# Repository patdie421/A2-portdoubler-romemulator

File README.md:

This card provide 2 functionalities :  
- duplicates the slot it uses into two horizontal slots (usefull in slot 7). I designed it to be able to use an A2DVI interface on Apple II computers where all the slots are occupied.  
- ROM emulation card (https://mirrors.apple2.org.za/ftp.apple.asimov.net/documentation/hardware/schematics/rom_emulator_card_050-0009-01_schematic.pdf). A friend ask me for a card capable of running Adrian Black's Deadtest ROM (https://github.com/misterblack1/appleII_deadtest). Since I had space on my slot splitter, I simply added three chips, and that was it. This first version is designed to use only the Deadtest ROM. Current restriction :
  - it did'nt allow to be controled by softwitch  
  - DMA IN/OUT are not supported (not needed when used in slot 7)  

  A version of the card currently under development will provide all the functionalities of a ROM card  
# Slot doubler  
This card is designed to allow the installation of two cards in a single slot. Although it can be installed in any slot, it is most effectively used as a splitter in slot 7. Since the two connectors are wired in parallel, not all card combinations are possible.
## kinds of Apple II cards
We can identify 3 kinds of cards :
- basic card : use soft switches, 16 addresses 0xC080+n\*0x10 to 0xC08F+n\*0x10, n=1 to 7, to interact whith the system. The card is activated by "Device Select" line.
- card with firmware locate at Cn00-CnFF (n=1 to 7), the "I/O Select" activated this kind of card when the firmware page is read or write. Most of this cards (if not all) use also soft switches at addresses C0N0x.  
- card "monitoring" the address bus (does not use device selection or I/O selection).  

## possible combinaisons

Different factors limit possible combinations :
- kind of card
- DMA or Interrupts
Other factors limit this combination, including the use of DMA and interrupt lines (/NMI and /INT).  
Before trying to install 2 cards in the doubled slots you have to know witch kind of cards you have.  

## working (tested) combinaisons
(to be done)

(usefull information can be fund here : https://grokipedia.com/page/apple_ii_peripheral_cards)

# Rom emulation card
The rom is activated when a jumper is set on JP4. Current version can only be used for Apple II deadtest ROM.  
Work is in progress to emulate all functionalities of Apple Rom Emulator Card (050-0009-01)  (https://mirrors.apple2.org.za/Apple%20II%20Documentation%20Project/Interface%20Cards/ROM%20Cards/Apple%20ROM%20Emulator%20Card/Photos/Apple%20ROM%20Card%20with%20ROM%20-%20Front.jpg))

2764 or 27128 Eprom (or pinout equivalent) can be used. Check Adrian's documentation for burning the ROM. Not that for 8K ROM (2764) you have to load into address $1800 or for 16K ROM (27128) to $3800.

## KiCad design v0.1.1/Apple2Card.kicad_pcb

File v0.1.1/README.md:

Update connector positions  
  
 Not tested now

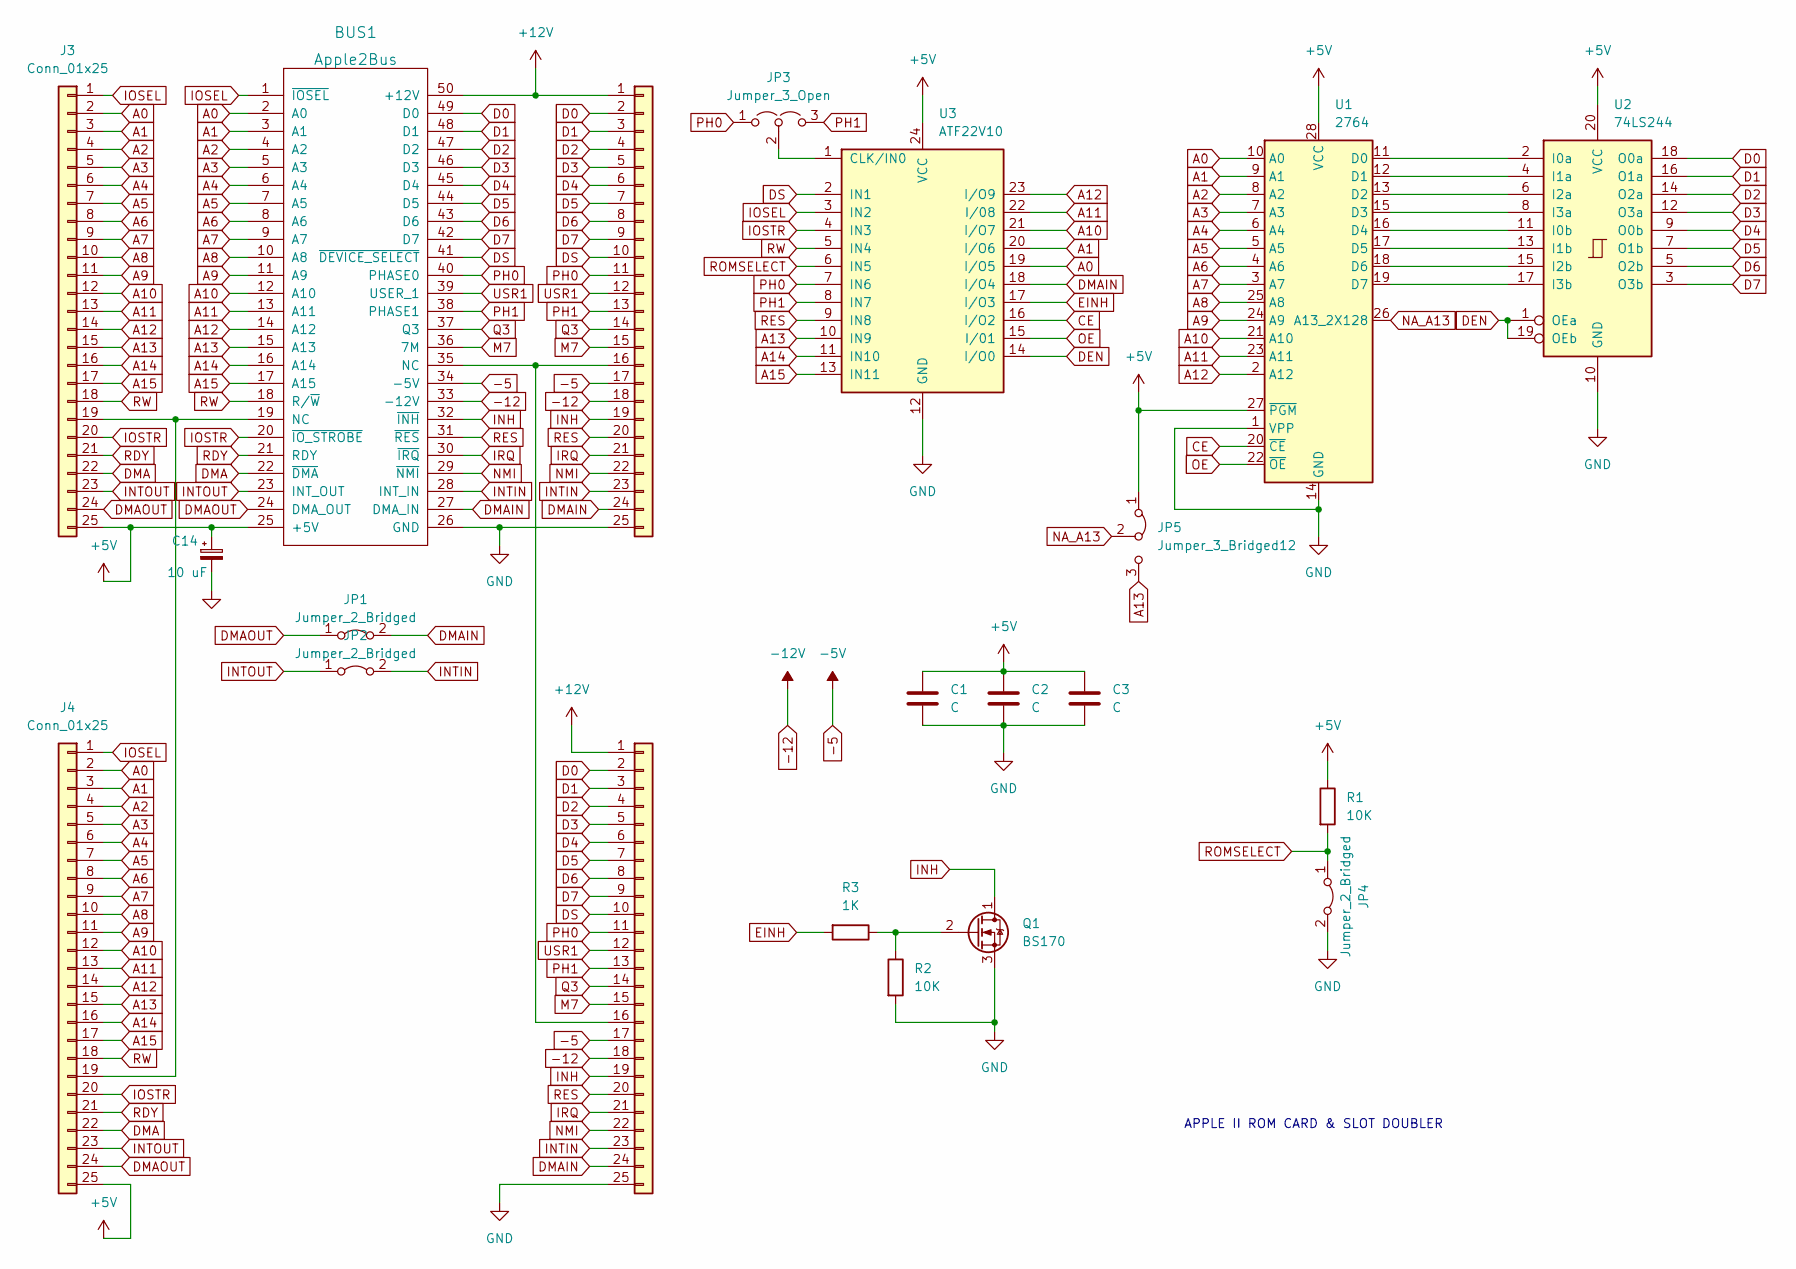
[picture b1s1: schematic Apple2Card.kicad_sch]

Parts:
BUS1: Apple2Bus; Apple2Slot
C1, C2, C3: C; C_Disc_D4.7mm_W2.5mm_P5.00mm
C14: 10 uF; CP_Radial_D5.0mm_P2.50mm
J1, J2, J3, J4: Conn_01x25; PinHeader_1x25_P2.54mm_Vertical
JP1, JP2, JP4: Jumper_2_Bridged; PinHeader_1x02_P2.54mm_Vertical
JP3: Jumper_3_Open; PinHeader_1x03_P2.54mm_Vertical
JP5: Jumper_3_Bridged12; SolderJumper-3_P1.3mm_Bridged12_RoundedPad1.0x1.5mm
Q1: BS170; TO-92_Inline
R1, R2: 10K; R_Axial_DIN0204_L3.6mm_D1.6mm_P7.62mm_Horizontal
R3: 1K; R_Axial_DIN0204_L3.6mm_D1.6mm_P7.62mm_Horizontal
U1: 2764; DIP-28_W15.24mm
U2: 74LS244; DIP-20_W7.62mm_Socket
U3: ATF22V10; DIP-24_W7.62mm_Socket

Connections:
+5V: BUS1.25 (+5V), C1.1, C2.1, C3.1, C14.1, J3.25, J4.25, JP5.1 (A), R1.1, U1.27 (~PGM), U1.28 (VCC), U2.20 (VCC), U3.24 (VCC)
+12V: BUS1.50 (+12V), J1.1, J2.1
-5: BUS1.34 (-5V), J1.17, J2.17
-12: BUS1.33 (-12V), J1.18, J2.18
A0: BUS1.2 (A0), J3.2, J4.2, U1.10 (A0), U3.19 (I/O5)
A1: BUS1.3 (A1), J3.3, J4.3, U1.9 (A1), U3.20 (I/O6)
A2: BUS1.4 (A2), J3.4, J4.4, U1.8 (A2)
A3: BUS1.5 (A3), J3.5, J4.5, U1.7 (A3)
A4: BUS1.6 (A4), J3.6, J4.6, U1.6 (A4)
A5: BUS1.7 (A5), J3.7, J4.7, U1.5 (A5)
A6: BUS1.8 (A6), J3.8, J4.8, U1.4 (A6)
A7: BUS1.9 (A7), J3.9, J4.9, U1.3 (A7)
A8: BUS1.10 (A8), J3.10, J4.10, U1.25 (A8)
A9: BUS1.11 (A9), J3.11, J4.11, U1.24 (A9)
A10: BUS1.12 (A10), J3.12, J4.12, U1.21 (A10), U3.21 (I/O7)
A11: BUS1.13 (A11), J3.13, J4.13, U1.23 (A11), U3.22 (I/08)
A12: BUS1.14 (A12), J3.14, J4.14, U1.2 (A12), U3.23 (I/O9)
A13: BUS1.15 (A13), J3.15, J4.15, JP5.3 (B), U3.10 (IN9)
A14: BUS1.16 (A14), J3.16, J4.16, U3.11 (IN10)
A15: BUS1.17 (A15), J3.17, J4.17, U3.13 (IN11)
CE: U1.20 (~CE), U3.16 (I/O2)
D0: BUS1.49 (D0), J1.2, J2.2, U2.18 (O0a)
D1: BUS1.48 (D1), J1.3, J2.3, U2.16 (O1a)
D2: BUS1.47 (D2), J1.4, J2.4, U2.14 (O2a)
D3: BUS1.46 (D3), J1.5, J2.5, U2.12 (O3a)
D4: BUS1.45 (D4), J1.6, J2.6, U2.9 (O0b)
D5: BUS1.44 (D5), J1.7, J2.7, U2.7 (O1b)
D6: BUS1.43 (D6), J1.8, J2.8, U2.5 (O2b)
D7: BUS1.42 (D7), J1.9, J2.9, U2.3 (O3b)
DEN: U2.1 (OEa), U2.19 (OEb), U3.14 (I/O0)
DMA: BUS1.22 (~DMA), J3.22, J4.22
DMAIN: BUS1.27 (DMA_IN), J1.24, J2.24, JP1.2 (B), U3.18 (I/O4)
DMAOUT: BUS1.24 (DMA_OUT), J3.24, J4.24, JP1.1 (A)
DS: BUS1.41 (~DEVICE_SELECT), J1.10, J2.10, U3.2 (IN1)
EINH: R3.2, U3.17 (I/O3)
GND: BUS1.26 (GND), C1.2, C2.2, C3.2, C14.2, J1.25, J2.25, JP4.2 (B), Q1.3 (S), R2.2, U1.1 (VPP), U1.14 (GND), U2.10 (GND), U3.12 (GND)
INH: BUS1.32 (~INH), J1.19, J2.19, Q1.1 (D)
INTIN: BUS1.28 (INT_IN), J1.23, J2.23, JP2.2 (B)
INTOUT: BUS1.23 (INT_OUT), J3.23, J4.23, JP2.1 (A)
IOSEL: BUS1.1 (~IOSEL), J3.1, J4.1, U3.3 (IN2)
IOSTR: BUS1.20 (~IO_STROBE), J3.20, J4.20, U3.4 (IN3)
IRQ: BUS1.30 (~IRQ), J1.21, J2.21
M7: BUS1.36 (7M), J1.15, J2.15
NA_A13: JP5.2 (C), U1.26 (A13_2X128)
NMI: BUS1.29 (~NMI), J1.22, J2.22
unnamed: BUS1.35 (NC), J1.16, J2.16
unnamed: BUS1.19 (NC), J3.19, J4.19
unnamed: JP3.2 (C), U3.1 (CLK/IN0)
unnamed: Q1.2 (G), R2.1, R3.1
unnamed: U1.11 (D0), U2.2 (I0a)
unnamed: U1.12 (D1), U2.4 (I1a)
unnamed: U1.13 (D2), U2.6 (I2a)
unnamed: U1.15 (D3), U2.8 (I3a)
unnamed: U1.16 (D4), U2.11 (I0b)
unnamed: U1.17 (D5), U2.13 (I1b)
unnamed: U1.18 (D6), U2.15 (I2b)
unnamed: U1.19 (D7), U2.17 (I3b)
OE: U1.22 (~OE), U3.15 (I/01)
PH0: BUS1.40 (PHASE0), J1.11, J2.11, JP3.1 (A), U3.7 (IN6)
PH1: BUS1.38 (PHASE1), J1.13, J2.13, JP3.3 (B), U3.8 (IN7)
Q3: BUS1.37 (Q3), J1.14, J2.14
RDY: BUS1.21 (RDY), J3.21, J4.21
RES: BUS1.31 (~RES), J1.20, J2.20, U3.9 (IN8)
RW: BUS1.18 (R/~W), J3.18, J4.18, U3.5 (IN4)
USR1: BUS1.39 (USER_1), J1.12, J2.12
/ROMSELECT: JP4.1 (A), R1.2, U3.6 (IN5)

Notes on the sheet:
APPLE II ROM CARD & SLOT DOUBLER

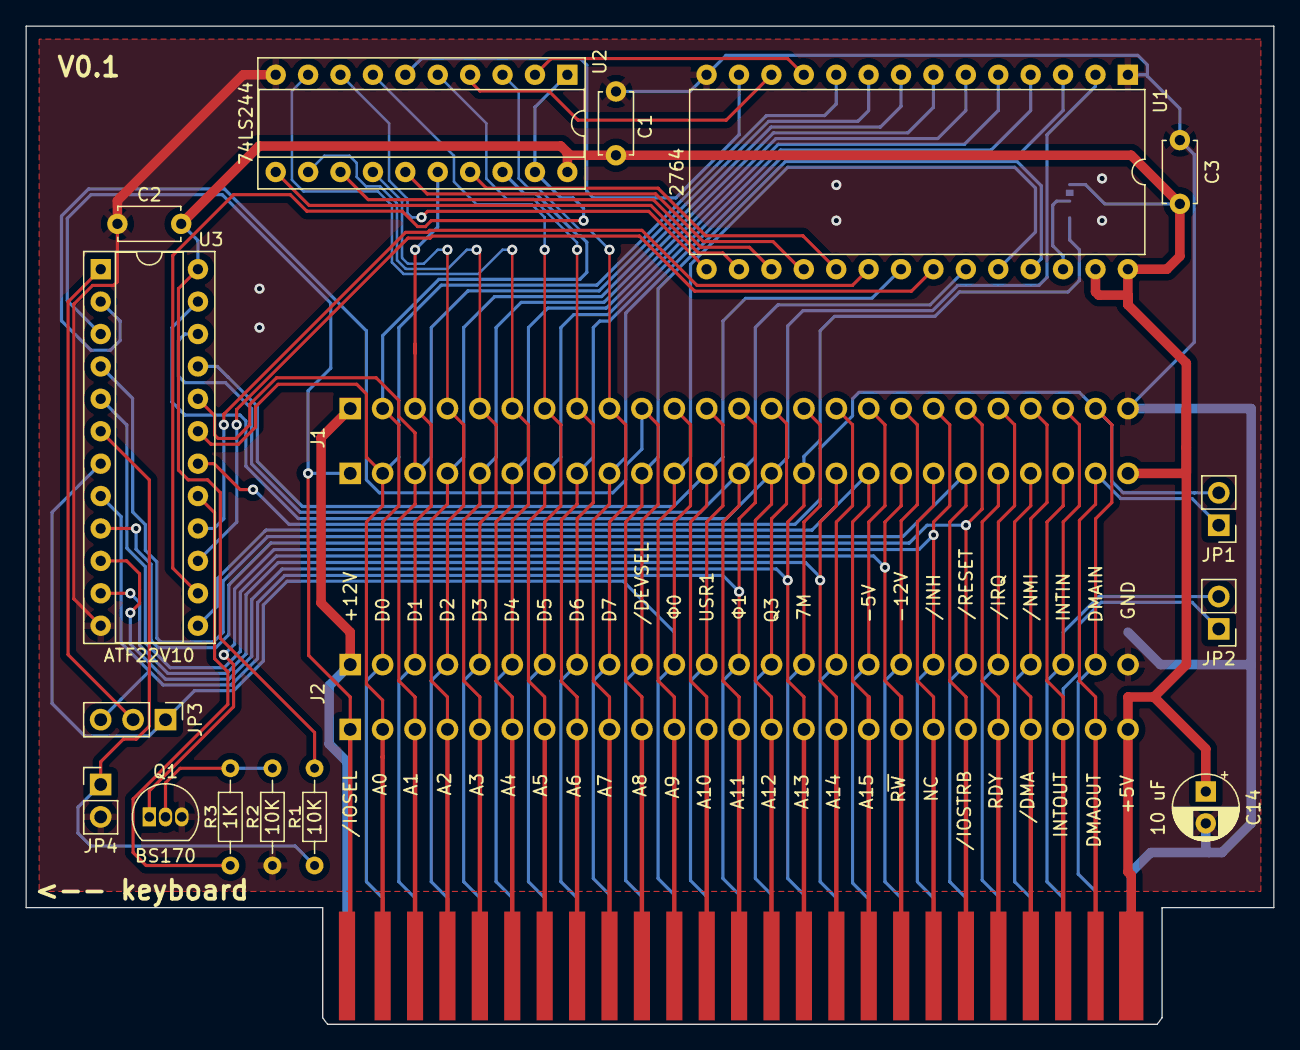
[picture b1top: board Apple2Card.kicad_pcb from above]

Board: 2 copper layers, 97.8 x 78.2 mm, 21 parts (1 on the bottom side), 66 nets.

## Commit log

2026-02-15 Initialize README file
2026-02-15 Refactor comments and enhance clarity in A2-rom-ctrl
    Updated comments and clarified Card Rom Enable jumper.
2026-02-15 Remove initial content from README.md
2026-02-18 Rename Gerber/Apple2Card-B_Cu.gbr to v0.1/Gerber/Apple2Card-B_Cu.gbr
2026-02-18 Rename Apple2Card.kicad_pcb to v0.1/Apple2Card.kicad_pcb
2026-02-18 Rename Apple2Card.kicad_prl to v0.1/Apple2Card.kicad_prl
2026-02-18 Rename Apple2Card.kicad_pro to v0.1/Apple2Card.kicad_pro
2026-02-18 Rename Apple2Card.kicad_sch to v0.1/Apple2Card.kicad_sch
2026-02-18 Rename Apple2Card.pdf to v0.1/Apple2Card.pdf
2026-02-18 Rename Apple2Card.png to v0.1/Apple2Card.png
2026-02-18 Rename IMG_3796.jpeg to v0.1/IMG_3796.jpeg
2026-02-18 Rename Gerber/Apple2Card-B_Mask.gbr to v0.1/Gerber/Apple2Card-B_Mask.gbr
2026-02-18 Rename Gerber/Apple2Card-B_Silkscreen.gbr to v0.1/Gerber/Apple2Card-B_Silkscreen.gbr
2026-02-18 Rename Gerber/Apple2Card-Edge_Cuts.gbr to v0.1/Gerber/Apple2Card-Edge_Cuts.gbr
2026-02-18 Rename Apple2Card-F_Cu.gbr to GerberApple2Card-F_Cu.gbr
2026-02-18 Rename v0.1/GerberApple2Card-F_Cu.gbr to v0.1/Gerber/Apple2Card-F_Cu.gbr
2026-02-18 Rename Gerber/Apple2Card-F_Mask.gbr to v0.1/Gerber/Apple2Card-F_Mask.gbr
2026-02-18 Rename Gerber/Apple2Card-F_Silkscreen.gbr to v0.1/Gerber/Apple2Card-F_Silkscreen.gbr
2026-02-18 Rename Gerber/Apple2Card-NPTH.drl to v0.1/Gerber/Apple2Card-NPTH.drl
2026-02-18 Rename Gerber/Apple2Card-PTH.drl to v0.1/Gerber/Apple2Card-PTH.drl
2026-02-18 Create pl
2026-02-18 Rename pl to A2-rom-ctrl.pld
2026-02-21 Fix typos and enhance README content
    Corrected minor typos and improved clarity in the README.
2026-02-21 Fix typo in ROM emulation card description
    Corrected typo in the description of the ROM emulation card.
2026-04-01 spacement correction
2026-04-01 remove not relevant files
